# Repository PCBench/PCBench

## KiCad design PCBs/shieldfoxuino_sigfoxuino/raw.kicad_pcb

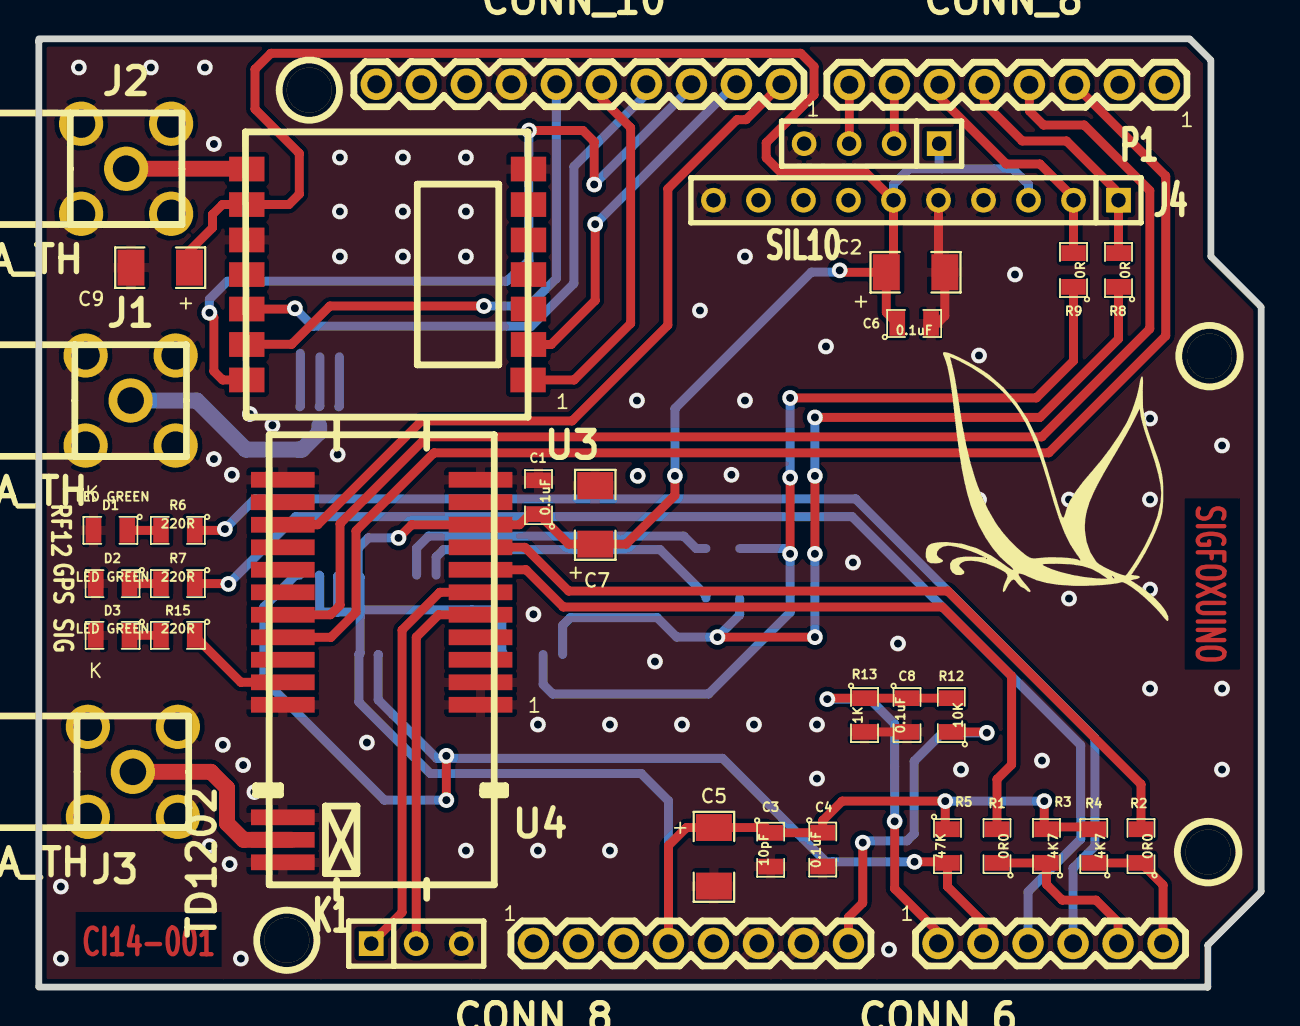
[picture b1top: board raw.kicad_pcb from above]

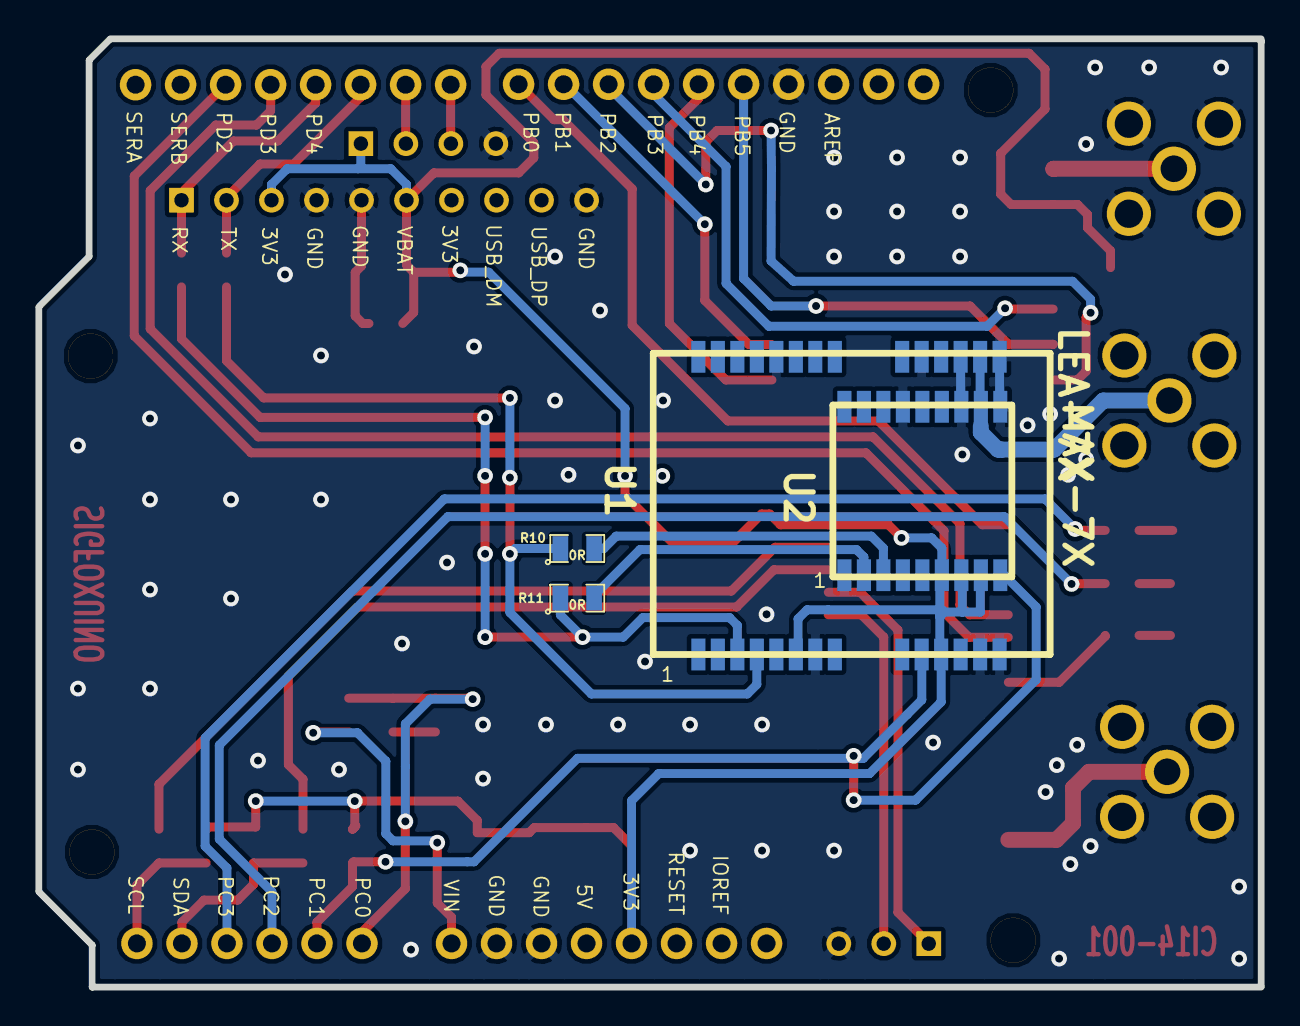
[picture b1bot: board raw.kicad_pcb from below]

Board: 2 copper layers, 69.0 x 53.5 mm, 42 parts (4 on the bottom side), 36 nets.

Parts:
C1, C4, C6, C8: 0.1uF; SM0805
C2, C5, C7: 10uF/9V; SM1206
C3: 10pF; SM0805
C9: 1uF/9V; SM1206
CON6_1: CONN_6; Con6
CON8_2: CONN_8; Con8
CONN8_1: CONN_8; Con8
CONN10_1: CONN_10; Con10
D1, D2, D3: LED GREEN; SM0805
J1, J2, J3: SMA_TH; SMA-SMB_right_angle
J4: SIL10; SIL-10
K1: CONN_3; SIL-3
P1: CONN_4; SIL-4
R1, R2: 0R0; SM0805
R3, R4: 4K7; SM0805
R5: 47K; SM0805
R6, R7, R15: 220R; SM0805
R8, R9, R10, R11: 0R; SM0805
R12: 10K; SM0805
R13: 1K; SM0805
U1: LEA-7X; LEA-xx
U2: MAX-7X; MAX-xx
U3: RFM12
U4: TD1202
V4, V5: 1pin

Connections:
+3.3V: C1.1, C2.1, C3.1, C4.1, C5.1, C6.1, C7.1, C9.1, CONN8_1.4, J4.3, J4.6, P1.1, R3.2, R4.2, R5.1, U1.6, U1.11, U2.6, U2.7, U2.8, U3.9, U4.9
/PB0: CONN10_1.1, U4.14
/PB1: CONN10_1.2, U3.2
/PB2: CONN10_1.3, U3.14
/PB3: CONN10_1.4, U3.12
/PB4: CONN10_1.5, U3.1
/PB5: CONN10_1.6, U3.13
/PC0: C8.1, CON6_1.1, R12.2, R13.1
/PC1: CON6_1.2, R5.2, U1.10, U2.9
/PC2: CON6_1.3, R7.1
/PC3: CON6_1.4, R6.1
/PD2: CON8_2.3, U4.19
/PD3: CON8_2.4, U4.18
/PD4: CON8_2.5, J4.1, R8.2
/PD5: CON8_2.6, J4.2, R9.2
/PD6: CON8_2.7, P1.2
/PD7: CON8_2.8, P1.3
/RF_GPS: J1.1, U1.16, U2.11
/RF_RF12: J2.1, U3.8
/RF_SIG: J3.1, U4.24
/RX_SFT: R8.1, R11.1, U1.3
/SCL: CON6_1.6, R2.1, R4.1
/SDA: CON6_1.5, R1.1, R3.1
/STATUS_SIG: R15.1, U4.21
/TX_SFT: R9.1, R10.1, U1.4
/VIN: CONN8_1.8, R12.1
GND: C1.2, C2.2, C3.2, C4.2, C5.2, C6.2, C7.2, C8.2, C9.2, CONN8_1.6, CONN8_1.7, CONN10_1.7, D1.2, D2.2, D3.2, J1.2, J1.3, J1.4, J1.5, J2.2, J2.3, J2.4, J2.5, J3.2, J3.3, J3.4, J3.5, J4.4, J4.5, J4.10, K1.3, P1.4, R13.2, U1.7, U1.13, U1.14, U1.15, U1.17, U1.19, U1.24, U2.1, U2.10, U2.12, U2.15, U3.7, U3.10, U4.1, U4.2, U4.11, U4.12, U4.22, U4.23, U4.25
unnamed: R11.2, U2.2
unnamed: R10.2, U2.3
unnamed: D2.1, R7.2
unnamed: D1.1, R6.2
unnamed: K1.2, U4.5
unnamed: K1.1, U4.6
unnamed: D3.1, R15.2
unnamed: R2.2, U4.8
unnamed: R1.2, U4.7

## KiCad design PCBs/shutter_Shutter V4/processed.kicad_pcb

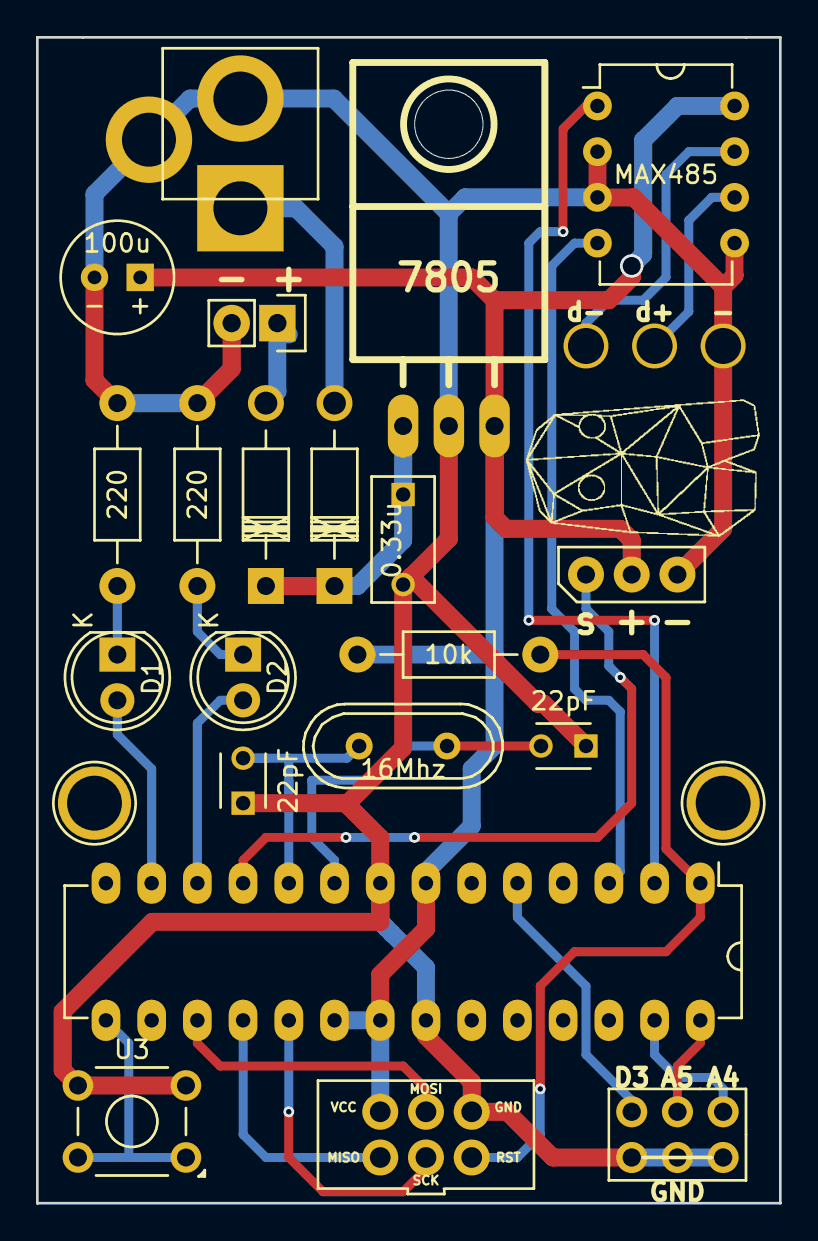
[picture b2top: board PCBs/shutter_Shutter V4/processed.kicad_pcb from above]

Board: 2 copper layers, 41.3 x 64.8 mm, 23 parts (0 on the bottom side), 24 nets.

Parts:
C1, C2: 22pF; C_Disc_D3_P2.5
C3: 100u; CP_VERT_6.3
C4: 0.33u; C_Rect_L7_W3.5_P5
CON1: AVR-ISP-6; CONN_ISP_6
CON2: BARREL_JACK; JACK_ALIM
D1, D2: LED; LED-5MM
D3, D4: 1N4004; Diode_DO-41_SOD81_Horizontal_RM10
IC1: ATMEGA328-P; DIP-28_W7.62mm_LongPads
K1: XLR3; CONN_075_3
LOGO: LOGO
P1: CONN_SERVO
P2: CONN_01X02; Pin_Header_Straight_1x02
P3: CONN_02X03; Pin_Header_Straight_2x03
R1: 10k; Resistor_Horizontal_RM10mm
R2, R3: 220; Resistor_Horizontal_RM10mm
U1: MAX485; DIP-8_W7.62mm
U2: 7805; TO220_HORYZ
U3: DIP_SWITCH; SW_TH_Tactile_Omron_B3F-10xx
Y1: 16Mhz; Crystal_HC49-U_Vertical

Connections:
/A4: IC1.27, P3.1
/A5: IC1.28, P3.3
/D+: K1.3, U1.6
/D-: K1.2, U1.7
/DMX_LEARN: IC1.15, U3.1, U3.2
/DMX_RX: IC1.2, U1.1
/DMX_TX: IC1.3, U1.4
/MISO: CON1.1, IC1.18
/MOSI: CON1.4, IC1.17
/PWM_OUT_3: IC1.5, P3.5
/RST: CON1.5, IC1.1, R1.2
/SCK: CON1.3, IC1.19
/SERVO: IC1.11, P1.1
GND: C1.1, C2.1, C3.2, C4.2, CON1.6, CON2.2, CON2.3, IC1.8, IC1.22, K1.1, P1.3, P2.2, P3.2, P3.4, P3.6, R2.2, R3.2, U1.2, U1.3, U1.5, U2.2, U3.3, U3.4
unnamed: C1.2, IC1.9, Y1.1
unnamed: C2.2, IC1.10, Y1.2
unnamed: C4.1, D3.1, D4.1, U2.1
unnamed: CON2.1, D3.2
unnamed: D1.1, R2.1
unnamed: D1.2, IC1.13
unnamed: D2.1, R3.1
unnamed: D2.2, IC1.12
unnamed: D4.2, P2.1
VCC: C3.1, CON1.2, IC1.7, IC1.20, IC1.21, P1.2, R1.1, U1.8, U2.3

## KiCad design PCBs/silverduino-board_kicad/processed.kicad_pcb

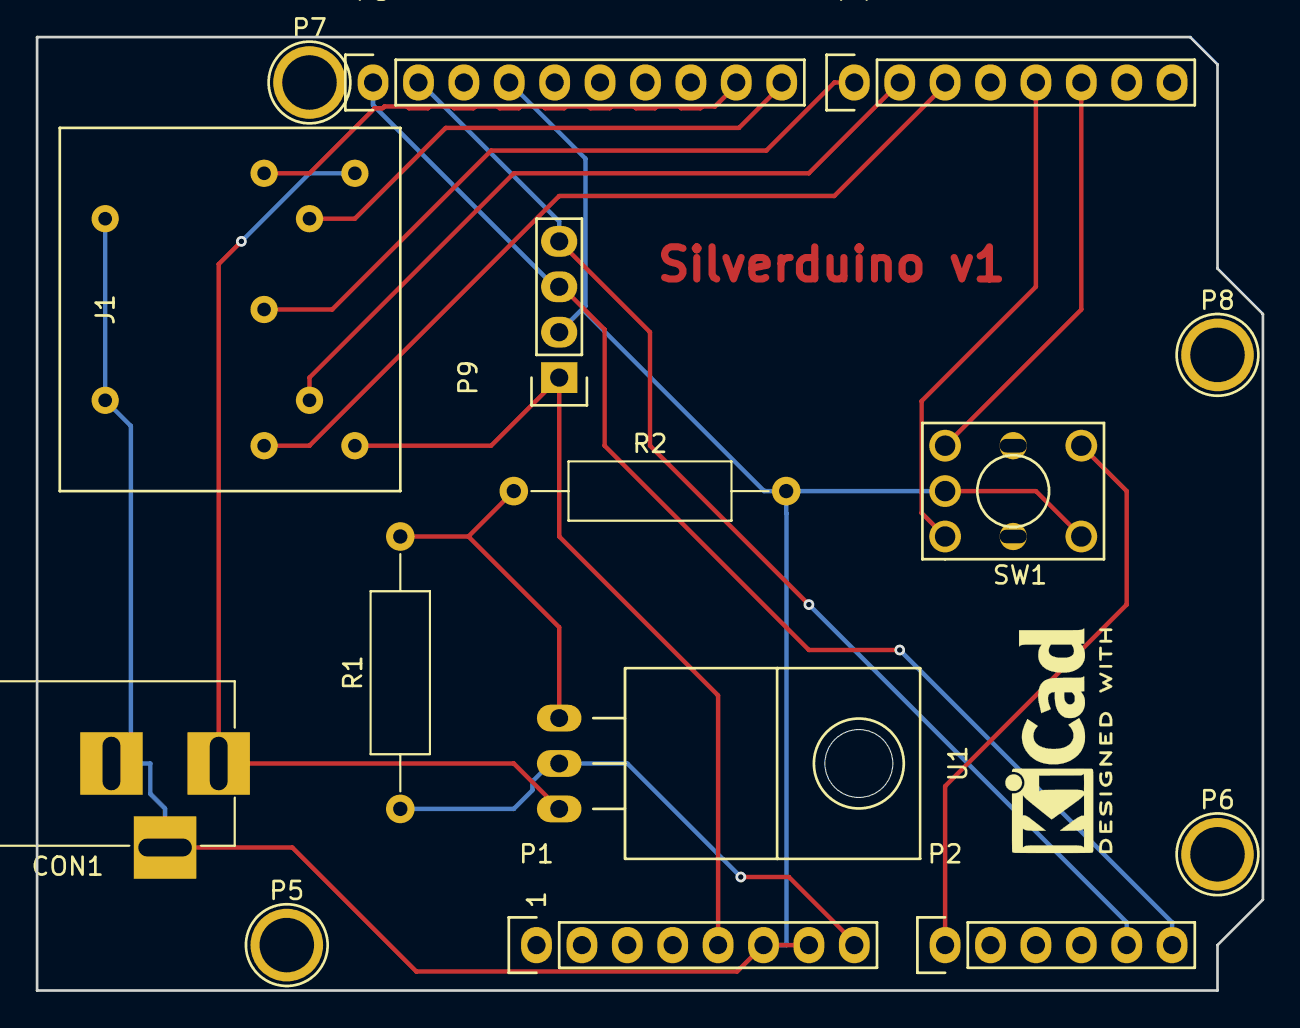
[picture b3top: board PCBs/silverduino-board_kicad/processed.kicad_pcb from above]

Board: 2 copper layers, 68.6 x 53.3 mm, 15 parts (0 on the bottom side), 15 nets.

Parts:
CON1: BARREL_JACK
J1: DIN-7; DIN-7_Angled
P1: Power; Socket_Strip_Arduino_1x08
P2: Analog; Socket_Strip_Arduino_1x06
P3: Digital; Socket_Strip_Arduino_1x10
P4: Digital; Socket_Strip_Arduino_1x08
P5, P6, P7, P8: CONN_01X01; Arduino_1pin
P9: CONN_01X04; Socket_Strip_Straight_1x04
R1: 330; R_Axial_DIN0309_L9.0mm_D3.2mm_P15.24mm_Horizontal
R2: 1k8; R_Axial_DIN0309_L9.0mm_D3.2mm_P15.24mm_Horizontal
SW1: Rotary_Encoder_Switch; Rotary_encoder_tactile
U1: LM317T; TO-220_Neutral123_Horizontal

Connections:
+5V: J1.7, P1.5, P9.1
+16V: CON1.1, J1.6, U1.3
/2: P4.6, SW1.1
/3(**): P4.5, SW1.3
/5(**): J1.3, P4.3
/6(**): J1.5, P4.2
/7: J1.2, P4.1
/8: J1.4, P3.10
/9(**): J1.1, P3.9
/A0: P2.1, SW1.4
/A4(SDA): P2.5, P3.2, P9.4
/A5(SCL): P2.6, P3.1, P9.3
/Vin: P1.8, R1.1, U1.2
GND: CON1.2, CON1.3, J1.SLVE, P1.6, P1.7, P3.4, P9.2, R2.2, SW1.2, SW1.5
unnamed: R1.2, R2.1, U1.1

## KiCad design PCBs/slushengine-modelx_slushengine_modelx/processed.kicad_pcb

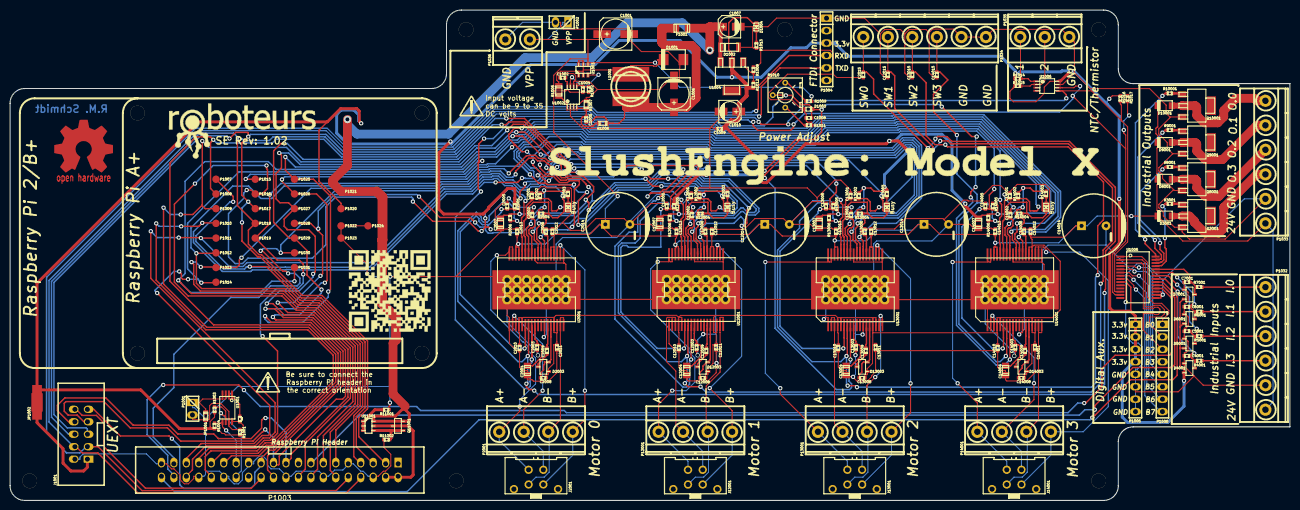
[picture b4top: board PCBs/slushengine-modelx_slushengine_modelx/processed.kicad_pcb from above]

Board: 2 copper layers, 261.0 x 100.0 mm, 216 parts (0 on the bottom side), 117 nets.

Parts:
C101, C1002, C1005, C1009, C2001, C2002, C2003, C2005, C2006, C2010, C2011, C2012, C2013, C2015, C12001, C12002, C12003, C12005, C12006, C12010, C12011, C12012, C12013, C12015, C13001, C13002, C13003, C13005, C13006, C13010, C13011, C13012, C13013, C13015, C14001, C14002, C14003, C14005, C14006, C14010, C14011, C14012, C14013, C14015: 0.1uf; c_0402
C1001: 50uf/50v; c_elec_6.3x7.7
C1004: 1nf; c_0402
C1006: 100uf/10v; c_elec_6.3x7.7
C1007, C1010: 10uf/6.3V; c_elec_4x5.3
C1008: 33nF; c_0402
C2004, C12004, C13004, C14004: 10uF; c_0805
C2007, C12007, C13007, C14007: 47uF; c_0805
C2008, C12008, C13008, C14008: 220nF; c_0402
C2009, C12009, C13009, C14009: 10nF; c_0402
C2014, C12014, C13014, C14014: 100uF; CP_12.5x25mm
C4001, C5001, C6001, C7001: 1nF; c_0402
D1001: DIODESCH; do214aa
D1002: ZENER; sod80c
D1003: 3.3V; sod523
D1004: LED; Led_0603
D2002, D12002, D13002, D14002: Busy; Led_0603
D2003, D12003, D13003, D14003: DOUBLE_SCHOTTKY; sot23
D3001, D8001, D9001, D10001: RSX501L-20TE25; do219ab
D4001, D5001, D6001, D7001: 1SS295; sot23
F1001: 2A; r_1206
J1001: UEXT1; vasch_strip_5x2
J2001, J12001, J13001, J14001: Stepper Motor; SureStep_CONN
JP1001: JUMPER; r_0603
JP1002: JUMPER; NetTie-I_Connected_SMD
L1001: 22uH; inductor_smd_8x5mm
MountingHole_3mm, MountingHole_3mm_2, MountingHole_3mm_3, MountingHole_3mm_4, MountingHole_3mm_5, MountingHole_3mm_6, MountingHole_3mm_7, MountingHole_3mm_8, MountingHole_3mm_9, MountingHole_3mm_10: VAL**; MountingHole_3mm
P1001, P1002: CONN_01X02; pin_strip_2
P1003: Raspberry_Pi_+_Conn; vasch_strip_20x2
P1004: CONN_01X06; pin_strip_6
P1005, P1006: CONN_01X08; pin_strip_8
P1007, P1008, P1009, P1010, P1011, P1012, P1013, P1014, P1015, P1016, P1017, P1018, P1019, P1020, P1021, P1022, P1023, P1024, P1025, P1026, P1027, P1028, P1029, P1030, P1031: TST; Measurement_Point_Round-SMD-Pad_Small
P1032, P1033, P1034: CONN_01X06; mkds_1,5-6
P1035: CONN_01X03; mkds_1,5-3
P1036: CONN_01X02; mkds_1,5-2
P2001, P12001, P13001, P14001: CONN_01X04; mkds_1,5-4
Q3001, Q8001, Q9001, Q10001: BCP51; sot223
Q11001: DMG2305; sot23
R1001: 1k; r_0402
R1002: 24k; r_0402
R1003, R1004, R1016, R1017: 3.9k; r_0402
R1005: 270; r_0805
R1006: 30k; r_0603
R1007: 10k; r_0603
R1008: 390; r_0402
R1009, R4001, R5001, R6001, R7001: 3.3k; r_0402
R1010: 22k; 25PR20KLF
R1011: 820; r_0402
R1012: 240; r_0402
R1013: 316; r_0402
R1014, R1015: 51k; r_0402
R2002, R2004, R2005, R12002, R12004, R12005, R13002, R13004, R13005, R14002, R14004, R14005: 39k; r_0402
R2003, R12003, R13003, R14003: 220; r_0402
R2006, R11001, R12006, R13006, R14006: 10k; r_0402
R3001, R8001, R9001, R10001: 470; r_0402
R11002: 47k; r_0402
U1001: CAT24C32HU4I-GT3; tssop-8
U1002: LM3489; msoic-8
U1003: FDC5614P; sot23-6
U1004: LM1117IMPX-ADJ; sot223
U1005: MCP23017; ssop-28
U1006: MAX1164x; msoic-8
U2001, U12001, U13001, U14001: L6470; POWERSO-36
U11001: DMMT5401; sot23-6

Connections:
+3V3: C101.1, C1009.1, C1010.1, C2006.1, C2007.1, C12006.1, C12007.1, C13006.1, C13007.1, C14006.1, C14007.1, D1004.1, D4001.3, D5001.3, D6001.3, D7001.3, JP1002.2, P1004.3, P1005.1, P1005.2, P1005.3, P1005.4, P1020.1, R1001.1, R1003.1, R1004.1, R1012.1, R1014.1, R1015.1, R1016.1, R1017.1, R2002.1, R2003.1, R2004.1, R2005.1, R2006.1, R12002.1, R12003.1, R12004.1, R12005.1, R12006.1, R13002.1, R13003.1, R13004.1, R13005.1, R13006.1, R14002.1, R14003.1, R14004.1, R14005.1, R14006.1, U1001.8, U1004.2, U1005.9, U1006.8, U2001.24, U12001.24, U13001.24, U14001.24
+5V: C1007.1, D1002.2, F1001.2, P1021.1, Q11001.3, U1004.3, U11001.6
+24V: C1001.1, C1002.1, C1004.1, C2008.2, C2010.1, C2011.1, C2012.1, C2013.1, C2014.1, C12008.2, C12010.1, C12011.1, C12012.1, C12013.1, C12014.1, C13008.2, C13010.1, C13011.1, C13012.1, C13013.1, C13014.1, C14008.2, C14010.1, C14011.1, C14012.1, C14013.1, C14014.1, D2003.1, D3001.2, D8001.2, D9001.2, D10001.2, D12003.1, D13003.1, D14003.1, P1002.1, P1032.1, P1033.1, P1036.1, R1002.1, R1009.1, U1002.8, U1003.4, U2001.4, U2001.5, U2001.15, U2001.16, U2001.22, U2001.23, U2001.33, U2001.34, U12001.4, U12001.5, U12001.15, U12001.16, U12001.22, U12001.23, U12001.33, U12001.34, U13001.4, U13001.5, U13001.15, U13001.16, U13001.22, U13001.23, U13001.33, U13001.34, U14001.4, U14001.5, U14001.15, U14001.16, U14001.22, U14001.23, U14001.33, U14001.34
/Back Power Protection/5V_MCU: P1003.2, P1003.4, Q11001.2, U11001.5
/IO_EXP_INTA: P1003.40, U1005.20
/IO_EXP_INTB: P1003.15, U1005.19
/IO_EXP_RST: P1003.38, U1005.18
/Industrial Input 0/A/D_Input: P1032.3, R4001.1
/Industrial Input 0/MCU_Input: C4001.1, D4001.2, R4001.2, U1005.21
/Industrial Input 1/A/D_Input: P1032.4, R5001.1
/Industrial Input 1/MCU_Input: C5001.1, D5001.2, R5001.2, U1005.22
/Industrial Input 2/A/D_Input: P1032.5, R6001.1
/Industrial Input 2/MCU_Input: C6001.1, D6001.2, R6001.2, U1005.23
/Industrial Input 3/A/D_Input: P1032.6, R7001.1
/Industrial Input 3/MCU_Input: C7001.1, D7001.2, R7001.2, U1005.24
/Industrial Output 0/MCU_Pin: R3001.1, U1005.25
/Industrial Output 0/Sink: D3001.1, P1033.3, Q3001.2
/Industrial Output 1/MCU_Pin: R8001.1, U1005.26
/Industrial Output 1/Sink: D8001.1, P1033.4, Q8001.2
/Industrial Output 2/MCU_Pin: R9001.1, U1005.27
/Industrial Output 2/Sink: D9001.1, P1033.5, Q9001.2
/Industrial Output 3/MCU_Pin: R10001.1, U1005.28
/Industrial Output 3/Sink: D10001.1, P1033.6, Q10001.2
/PI_I2C_SCL: J1001.5, P1003.5, P1017.1, R1016.2, U1005.12, U1006.5
/PI_I2C_SDA: J1001.6, P1003.3, P1018.1, R1017.2, U1005.13, U1006.6
/PI_SPI_CE0: J1001.10, P1003.24
/PI_UART_RXD: J1001.3, P1003.10, P1004.4
/PI_UART_TXD: J1001.4, P1003.8, P1004.5
/Stepper Driver #0/ADCIN: C1008.1, D1003.2, P1015.1, R1010.2, U2001.8, U12001.8, U13001.8, U14001.8
/Stepper Driver #0/SCK: J1001.9, P1003.23, P1025.1, U2001.26, U12001.26, U13001.26, U14001.26
/Stepper Driver #0/SDI: J1001.8, P1003.19, P1027.1, U2001.27, U12001.27, U13001.27, U14001.27
/Stepper Driver #0/SDO: J1001.7, P1003.21, P1026.1, U2001.25, U12001.25, U13001.25, U14001.25
/Stepper Driver #0/STCK: P1003.7, P1007.1, U2001.32
/Stepper Driver #0/SWITCH: C2015.1, P1034.6, R2006.2, U2001.7
/Stepper Driver #0/VREG: C2003.1, C2004.1, U2001.9
/Stepper Driver #0/~BUSY~/SYNC: C2002.1, D2002.2, P1003.36, P1011.1, R2004.2, U2001.29
/Stepper Driver #0/~CS: P1003.18, P1028.1, U2001.30
/Stepper Driver #0/~FLAG: C2001.1, C12001.1, C13001.1, C14001.1, P1003.33, P1019.1, R2002.2, R12002.2, R13002.2, R14002.2, U2001.31, U12001.31, U13001.31, U14001.31
/Stepper Driver #0/~STBY/RST: C2005.1, C12005.1, C13005.1, C14005.1, P1003.16, P1016.1, R2005.2, R12005.2, R13005.2, R14005.2, U2001.6, U12001.6, U13001.6, U14001.6
/Stepper Driver #1/STCK: P1003.29, P1008.1, U12001.32
/Stepper Driver #1/SWITCH: C12015.1, P1034.5, R12006.2, U12001.7
/Stepper Driver #1/VREG: C12003.1, C12004.1, U12001.9
/Stepper Driver #1/~BUSY~/SYNC: C12002.1, D12002.2, P1003.11, P1012.1, R12004.2, U12001.29
/Stepper Driver #1/~CS: P1003.22, P1029.1, U12001.30
/Stepper Driver #2/STCK: P1003.31, P1009.1, U13001.32
/Stepper Driver #2/SWITCH: C13015.1, P1034.4, R13006.2, U13001.7
/Stepper Driver #2/VREG: C13003.1, C13004.1, U13001.9
/Stepper Driver #2/~BUSY~/SYNC: C13002.1, D13002.2, P1003.12, P1013.1, R13004.2, U13001.29
/Stepper Driver #2/~CS: P1003.37, P1030.1, U13001.30
/Stepper Driver #3/STCK: P1003.32, P1010.1, U14001.32
/Stepper Driver #3/SWITCH: C14015.1, P1034.3, R14006.2, U14001.7
/Stepper Driver #3/VREG: C14003.1, C14004.1, U14001.9
/Stepper Driver #3/~BUSY~/SYNC: C14002.1, D14002.2, P1003.35, P1014.1, R14004.2, U14001.29
/Stepper Driver #3/~CS: P1003.13, P1031.1, U14001.30
GND: C101.2, C1001.2, C1002.2, C1006.2, C1007.2, C1008.2, C1009.2, C1010.2, C2001.2, C2002.2, C2003.2, C2004.2, C2005.2, C2006.2, C2007.2, C2010.2, C2011.2, C2012.2, C2013.2, C2014.2, C2015.2, C4001.2, C5001.2, C6001.2, C7001.2, C12001.2, C12002.2, C12003.2, C12004.2, C12005.2, C12006.2, C12007.2, C12010.2, C12011.2, C12012.2, C12013.2, C12014.2, C12015.2, C13001.2, C13002.2, C13003.2, C13004.2, C13005.2, C13006.2, C13007.2, C13010.2, C13011.2, C13012.2, C13013.2, C13014.2, C13015.2, C14001.2, C14002.2, C14003.2, C14004.2, C14005.2, C14006.2, C14007.2, C14010.2, C14011.2, C14012.2, C14013.2, C14014.2, C14015.2, D1001.1, D1002.1, D1003.1, D4001.1, D5001.1, D6001.1, D7001.1, J1001.2, JP1001.2, P1001.1, P1002.2, P1003.6, P1003.9, P1003.14, P1003.20, P1003.25, P1003.30, P1003.34, P1003.39, P1004.1, P1005.5, P1005.6, P1005.7, P1005.8, P1022.1, P1023.1, P1024.1, P1032.2, P1033.2, P1034.1, P1034.2, P1035.1, P1036.2, Q3001.3, Q8001.3, Q9001.3, Q10001.3, R1007.2, R1008.2, R1011.2, R1013.2, R11001.2, R11002.2, U1001.1, U1001.2, U1001.3, U1001.4, U1002.2, U1002.6, U1005.10, U1005.15, U1005.16, U1005.17, U1006.7, U2001.1, U2001.12, U2001.19, U2001.28, U2001.PAD, U12001.1, U12001.12, U12001.19, U12001.28, U12001.PAD, U13001.1, U13001.12, U13001.19, U13001.28, U13001.PAD, U14001.1, U14001.12, U14001.19, U14001.28, U14001.PAD
unnamed: C1004.2, R1002.2, U1002.5
unnamed: C1005.1, C1006.1, F1001.1, L1001.2, R1006.1
unnamed: C1005.2, R1006.2, R1007.1, U1002.4
unnamed: C2008.1, D2003.3, U2001.14
unnamed: C2009.1, D2003.2
unnamed: C2009.2, U2001.13
unnamed: C12008.1, D12003.3, U12001.14
unnamed: C12009.1, D12003.2
unnamed: C12009.2, U12001.13
unnamed: C13008.1, D13003.3, U13001.14
unnamed: C13009.1, D13003.2
unnamed: C13009.2, U13001.13
unnamed: C14008.1, D14003.3, U14001.14
unnamed: C14009.1, D14003.2
unnamed: C14009.2, U14001.13
unnamed: D1001.2, L1001.1, R1005.1, U1003.1, U1003.2, U1003.5, U1003.6
unnamed: D1004.2, R1013.1
unnamed: D2002.1, R2003.2
unnamed: D12002.1, R12003.2
unnamed: D13002.1, R13003.2
unnamed: D14002.1, R14003.2
unnamed: J1001.1, JP1002.1
unnamed: J2001.1, P2001.1, U2001.35, U2001.36
unnamed: J2001.2, P2001.2, U2001.2, U2001.3
unnamed: J2001.3, P2001.3, U2001.17, U2001.18
unnamed: J2001.4, P2001.4, U2001.20, U2001.21
unnamed: J12001.1, P12001.1, U12001.35, U12001.36
unnamed: J12001.2, P12001.2, U12001.2, U12001.3
unnamed: J12001.3, P12001.3, U12001.17, U12001.18
unnamed: J12001.4, P12001.4, U12001.20, U12001.21
unnamed: J13001.1, P13001.1, U13001.35, U13001.36
unnamed: J13001.2, P13001.2, U13001.2, U13001.3
unnamed: J13001.3, P13001.3, U13001.17, U13001.18
unnamed: J13001.4, P13001.4, U13001.20, U13001.21
unnamed: J14001.1, P14001.1, U14001.35, U14001.36
unnamed: J14001.2, P14001.2, U14001.2, U14001.3
unnamed: J14001.3, P14001.3, U14001.17, U14001.18
unnamed: J14001.4, P14001.4, U14001.20, U14001.21
unnamed: JP1001.1, P1001.2, R1001.2, U1001.7
unnamed: P1003.27, R1004.2, U1001.5
unnamed: P1003.28, R1003.2, U1001.6
unnamed: P1006.1, U1005.1
unnamed: P1006.2, U1005.2
unnamed: P1006.3, U1005.3
unnamed: P1006.4, U1005.4
unnamed: P1006.5, U1005.5
unnamed: P1006.6, U1005.6
unnamed: P1006.7, U1005.7
unnamed: P1006.8, U1005.8
unnamed: P1035.2, R1015.2, U1006.2
unnamed: P1035.3, R1014.2, U1006.1
unnamed: Q3001.1, R3001.2
unnamed: Q8001.1, R8001.2
unnamed: Q9001.1, R9001.2
unnamed: Q10001.1, R10001.2
unnamed: Q11001.1, R11002.1, U11001.4
unnamed: R1005.2, U1002.1
unnamed: R1008.1, R1012.2, U1004.1
unnamed: R1009.2, R1010.1
unnamed: R1010.3, R1011.1
unnamed: R11001.1, U11001.1, U11001.2, U11001.3
unnamed: U1002.7, U1003.3

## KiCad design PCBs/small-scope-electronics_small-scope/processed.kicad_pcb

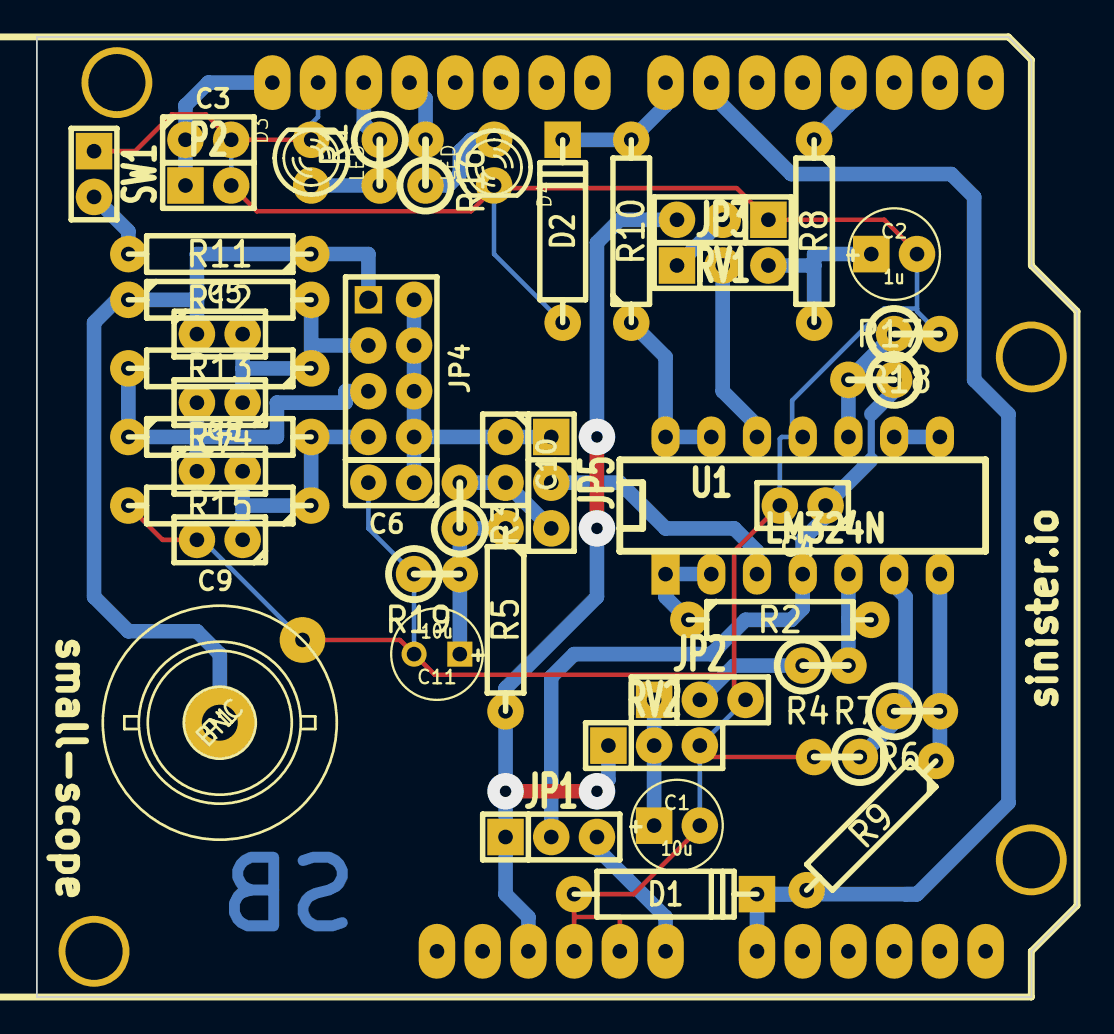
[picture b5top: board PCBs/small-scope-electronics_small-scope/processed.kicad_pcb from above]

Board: 2 copper layers, 57.8 x 53.3 mm, 46 parts (0 on the bottom side), 33 nets.

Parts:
C1, C11: 10u; C1V5
C2: 1u; C1V5
C3, C4: 1n; C1
C5: 16p; C1
C6: 10p; C1
C7: 130p; C1
C8, C9: 270p; C1
C10: 10u/35V; C1
D1, D2: 5.1V; D4
D3, D4: LED; LED-3MM
JP1: VDD SRC; SIL-3
JP2: DC BIAS; SIL-3
JP3: THR SRC; SIL-3
JP4: ATT SEL; pin_array_4x2
JP5: AC/DC; SIL-3
P1: BNC; BNCv
P2: AREF; SIL-2
R1, R16: 220; R1
R2, R5: 10k; R4-LARGE_PADS
R3, R4, R6, R7, R17, R18, R19: 10k; R1
R8: 1k8; R4-LARGE_PADS
R9, R10: 220; R4-LARGE_PADS
R11: 50; R4-LARGE_PADS
R12: 800k; R4-LARGE_PADS
R13: 100k; R4-LARGE_PADS
R14, R15: 50k; R4-LARGE_PADS
RV1, RV2: 10k; SIL-3
SHIELD1: ARDUINO_SHIELD
SW1: STAT DIS; SIL-2
U1: LM324N; DIP-14__300_ELL

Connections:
/2.5V: C11.1, R3.1, R5.1, R19.2
/BIAS: C1.1, JP2.1, RV2.2
/ERR_LED: R1.1, SHIELD1.13
/INFO_LED: R16.2, SHIELD1.12
/SIG_ACDC: JP5.2, U1.3
/SIG_ATT: C6.1, C10.1, JP4.2, JP4.4, JP4.6, JP4.8, JP5.1
/SIG_IN: C5.1, JP4.1, P1.1, R11.1, R12.1
/SIG_UC: D1.2, R9.2, SHIELD1.6, SHIELD1.AD0
/THR_IN: D2.2, R10.2, SHIELD1.7
/THR_OUT: R8.1, SHIELD1.3
/Vin: JP1.3, SHIELD1.V_IN
/x5: C5.2, C7.1, JP4.3, R12.2, R13.1
/x10: C7.2, C8.1, JP4.5, R13.2, R14.1
/x20: C8.2, C9.1, JP4.7, R14.2, R15.1
GND: C1.2, C2.2, C3.2, C4.2, C6.2, C9.2, C11.2, D1.1, D2.1, D3.2, D4.2, JP2.3, P1.2, P2.2, R7.2, R15.2, R18.2, R19.1, RV1.1, RV2.3, SHIELD1.GND1, SHIELD1.GND2, SHIELD1.GND3, SW1.1, U1.11
unnamed: R11.2, SW1.2
unnamed: JP3.2, U1.12
unnamed: JP3.1, RV1.2
unnamed: R2.1, U1.1, U1.2
unnamed: R2.2, R4.2, U1.5
unnamed: R6.1, R7.1, U1.6
unnamed: R6.2, R9.1, U1.7
unnamed: R10.1, U1.13, U1.14
unnamed: JP2.2, R4.1
unnamed: C3.1, P2.1, SHIELD1.AREF
unnamed: C10.2, JP5.3, R3.2
unnamed: R17.2, R18.1, U1.10
unnamed: D3.1, R1.2
unnamed: U1.8, U1.9
unnamed: D4.1, R16.1
unnamed: C2.1, JP3.3, R8.2
VCC: JP1.1, R5.2, RV1.3, RV2.1, SHIELD1.5V
VDD: C4.1, JP1.2, R17.1, U1.4

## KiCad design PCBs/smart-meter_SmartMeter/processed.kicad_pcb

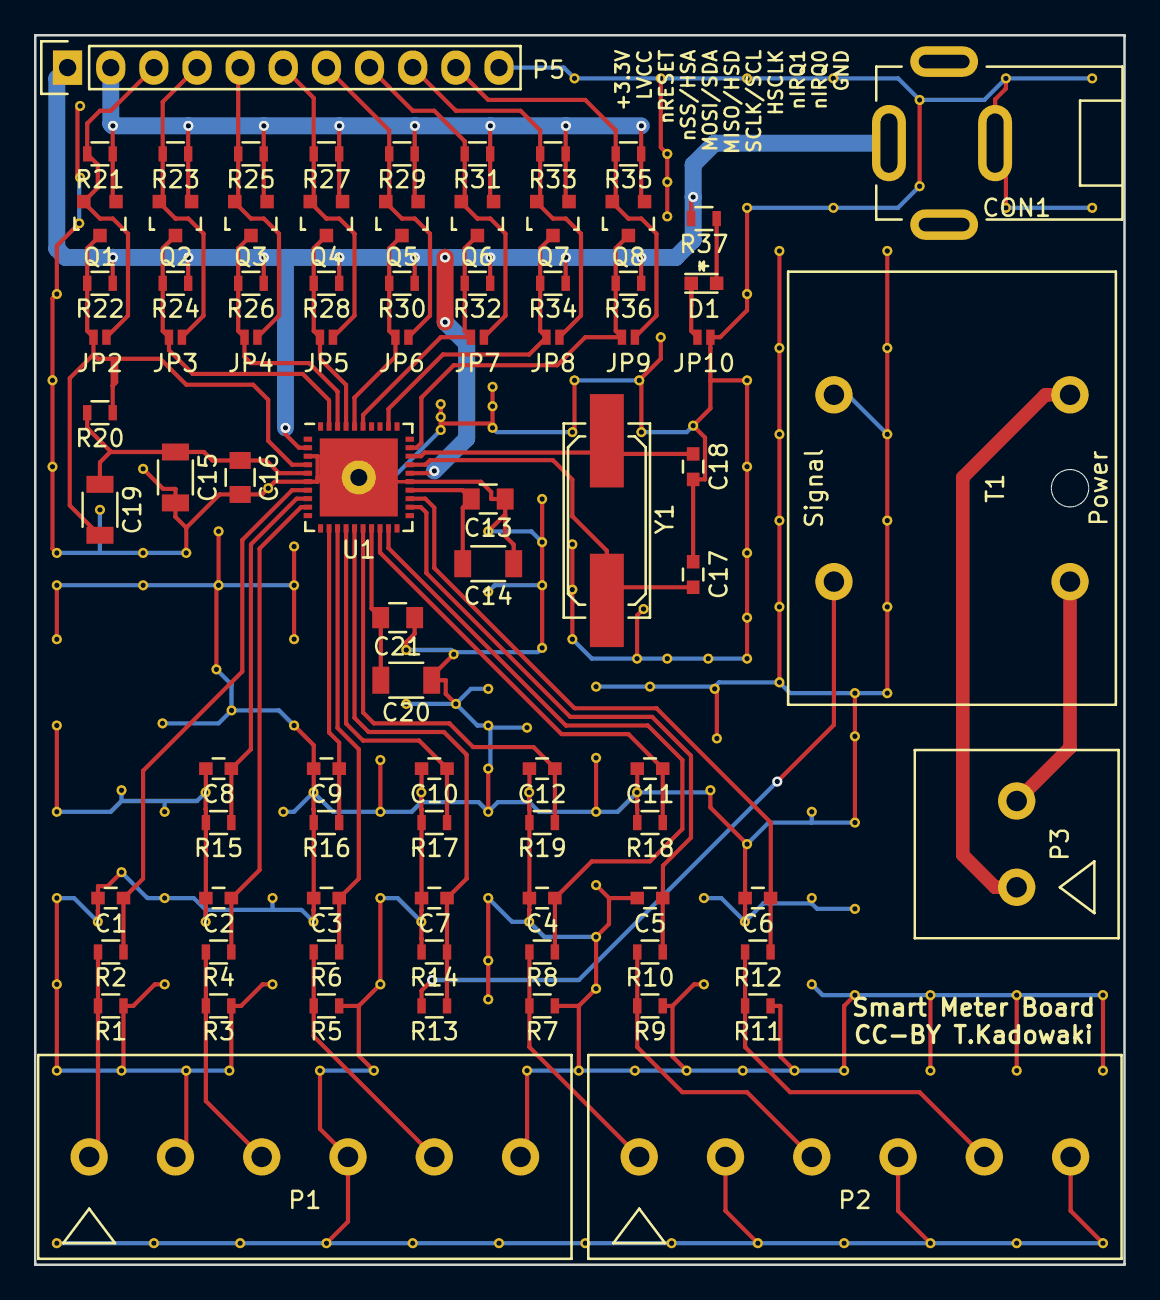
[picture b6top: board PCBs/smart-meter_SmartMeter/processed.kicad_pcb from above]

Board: 2 copper layers, 64.1 x 72.4 mm, 260 parts (0 on the bottom side), 48 nets.

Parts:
C1, C2, C3, C4, C5, C6, C7, C8, C9, C10, C11, C12: 22nF; C_0603
C13, C16: 0.22uF; C_0805
C14, C15, C20: 4.7uF; C_1206
C17, C18: 20pF; C_0603
C19: 1uF; C_1206
C21: 0.1uF; C_0805
CON1: BARREL_JACK; DC-Jack
D1: LED; LED-0603
JP1: Jumper_NC_Small; Jumper_Close
JP2, JP3, JP4, JP5, JP6, JP7, JP8, JP9, JP10: Jumper_NO_Small; Jumper
Noname_1, Noname_2, Noname_3, Noname_4, Noname_5, Noname_6, Noname_7, Noname_8, Noname_9, Noname_10, Noname_11, Noname_12, Noname_13, Noname_14, Noname_15, Noname_16, Noname_17, Noname_18, Noname_19, Noname_20, Noname_21, Noname_22, Noname_23, Noname_24, Noname_25, Noname_26, Noname_27, Noname_28, Noname_29, Noname_30, Noname_31, Noname_32, Noname_33, Noname_34, Noname_35, Noname_36, Noname_37, Noname_38, Noname_39, Noname_40, Noname_41, Noname_42, Noname_43, Noname_44, Noname_45, Noname_46, Noname_47, Noname_48, Noname_49, Noname_50, Noname_51, Noname_52, Noname_53, Noname_54, Noname_55, Noname_56, Noname_57, Noname_58, Noname_59, Noname_60, Noname_61, Noname_62, Noname_63, Noname_64, Noname_65, Noname_66, Noname_67, Noname_68, Noname_69, Noname_70, Noname_71, Noname_72, Noname_73, Noname_74, Noname_75, Noname_76, Noname_77, Noname_78, Noname_79, Noname_80, Noname_81, Noname_82, Noname_83, Noname_84, Noname_85, Noname_86, Noname_87, Noname_88, Noname_89, Noname_90, Noname_91, Noname_92, Noname_93, Noname_94, Noname_95, Noname_96, Noname_97, Noname_98, Noname_99, Noname_100, Noname_101, Noname_102, Noname_103, Noname_104, Noname_105, Noname_106, Noname_107, Noname_108, Noname_109, Noname_110, Noname_111, Noname_112, Noname_113, Noname_114, Noname_115, Noname_116, Noname_117, Noname_118, Noname_119, Noname_120, Noname_121, Noname_122, Noname_123, Noname_124, Noname_125, Noname_126, Noname_127, Noname_128, Noname_129, Noname_130, Noname_131, Noname_132, Noname_133, Noname_134, Noname_135, Noname_136, Noname_137, Noname_138, Noname_139, Noname_140, Noname_141, Noname_142, Noname_143, Noname_144, Noname_145, Noname_146, Noname_147, Noname_148, Noname_149, Noname_150, Noname_151, Noname_152, Noname_153, Noname_154, Noname_155, Noname_156, Noname_157, Noname_158, Noname_159, Noname_160, Noname_161, Noname_162, Noname_163, Noname_164, Noname_165, Noname_166, Noname_167, Noname_168, Noname_169, Noname_170, Noname_171, Noname_172, Noname_173, Noname_174: via
P1, P2: CONN_01X06; XW4E-06C1-S1
P3: CONN_01X02; XW4E-02C1-S1
P4: HEAT SINK; SolderWirePad_single_1-2mmDrill
P5: CONN_01X11; Pin_Header_Straight_1x11
Q1, Q2, Q3, Q4, Q5, Q6, Q7, Q8: BSS138; SOT-23
R1, R3, R5, R7, R9, R11: 33; R_0603
R2, R4, R6, R8, R10, R12, R13, R15, R16, R17, R18, R19, R37: 1K; R_0603
R14: 100; R_0603
R20, R21, R22, R23, R24, R25, R26, R27, R28, R29, R30, R31, R32, R33, R34, R35, R36: 10K; R_0603
T1: TRANSFO; VT2401-A01
U1: ADE7816; QFN-40-1EP_6x6mm_Pitch0.5mm
Y1: 16.384MHz; Q_49U3HMS

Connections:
+3V3: CON1.1, P5.1, R22.1, R24.1, R26.1, R28.1, R30.1, R32.1, R34.1, R36.1, R37.1, U1.2, U1.26
/AVDD: C13.1, C14.1, U1.24
/DVDD: C15.1, C16.1, C19.1, R20.1, U1.5
/LVCONV/H1: C19.2, JP2.2, Q1.3, R20.2, R22.2, U1.4
/LVCONV/H2: JP3.2, Q2.3, R24.2, U1.39
/LVCONV/H3: JP4.2, Q3.3, R26.2, U1.38
/LVCONV/H4: JP5.2, Q4.3, R28.2, U1.37
/LVCONV/H5: JP6.2, Q5.3, R30.2, U1.36
/LVCONV/H6: JP7.2, Q6.3, R32.2, U1.35
/LVCONV/H7: JP8.2, Q7.3, R34.2, U1.32
/LVCONV/H8: JP9.2, Q8.3, R36.2, U1.29
/LVCONV/L1: JP2.1, P5.3, Q1.2, R21.2
/LVCONV/L2: JP3.1, P5.4, Q2.2, R23.2
/LVCONV/L3: JP4.1, P5.5, Q3.2, R25.2
/LVCONV/L4: JP5.1, P5.6, Q4.2, R27.2
/LVCONV/L5: JP6.1, P5.7, Q5.2, R29.2
/LVCONV/L6: JP7.1, P5.8, Q6.2, R31.2
/LVCONV/L7: JP8.1, P5.9, Q7.2, R33.2
/LVCONV/L8: JP9.1, P5.10, Q8.2, R35.2
/LVCONV/LVCC: P5.2, Q1.1, Q2.1, Q3.1, Q4.1, Q5.1, Q6.1, Q7.1, Q8.1, R21.1, R23.1, R25.1, R27.1, R29.1, R31.1, R33.1, R35.1
/REF: C20.1, C21.1, U1.17
GNDA: C1.2, C2.2, C3.2, C4.2, C5.2, C6.2, C7.2, C8.2, C9.2, C10.2, C11.2, C12.2, C13.2, C14.2, C20.2, C21.2, JP1.1, P1.2, P1.4, P1.6, P2.2, P2.4, P2.6, R1.1, R3.1, R5.1, R7.1, R9.1, R11.1, R14.1, R15.2, R16.2, R17.2, R18.2, R19.2, T1.3, U1.25
GNDD: C15.2, C16.2, C17.2, C18.2, CON1.2, JP1.2, JP10.2, P4.1, P5.11, U1.3, U1.6, U1.41
unnamed: C1.1, R2.1, U1.7
unnamed: C2.1, R4.1, U1.9
unnamed: C3.1, R6.1, U1.13
unnamed: C4.1, R8.1, U1.19
unnamed: C5.1, R10.1, U1.22
unnamed: C6.1, R12.1, U1.23
unnamed: C7.1, R13.1, R14.2, U1.15
unnamed: C8.1, R15.1, U1.8
unnamed: C9.1, R16.1, U1.12
unnamed: C10.1, R17.1, U1.14
unnamed: C11.1, R18.1, U1.18
unnamed: C12.1, R19.1, U1.16
unnamed: C17.1, U1.27, Y1.2
unnamed: C18.1, U1.28, Y1.1
unnamed: D1.1, JP10.1
unnamed: D1.2, R37.2
unnamed: P1.1, R1.2, R2.2
unnamed: P1.3, R3.2, R4.2
unnamed: P1.5, R5.2, R6.2
unnamed: P2.1, R7.2, R8.2
unnamed: P2.3, R9.2, R10.2
unnamed: P2.5, R11.2, R12.2
unnamed: P3.1, T1.2
unnamed: P3.2, T1.1
unnamed: R13.2, T1.4

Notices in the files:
PCBs/smart-meter_SmartMeter/processed.kicad_pcb:
CC-BY T.Kadowaki
